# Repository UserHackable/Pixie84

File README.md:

## Pixie84 

### Board dimensions

* (160000, 80000) original units
* (1.6000, 0.8000) inches
* (40.6400, 20.3200) mm

| Front | Back |
| --- | --- |
|  |  |

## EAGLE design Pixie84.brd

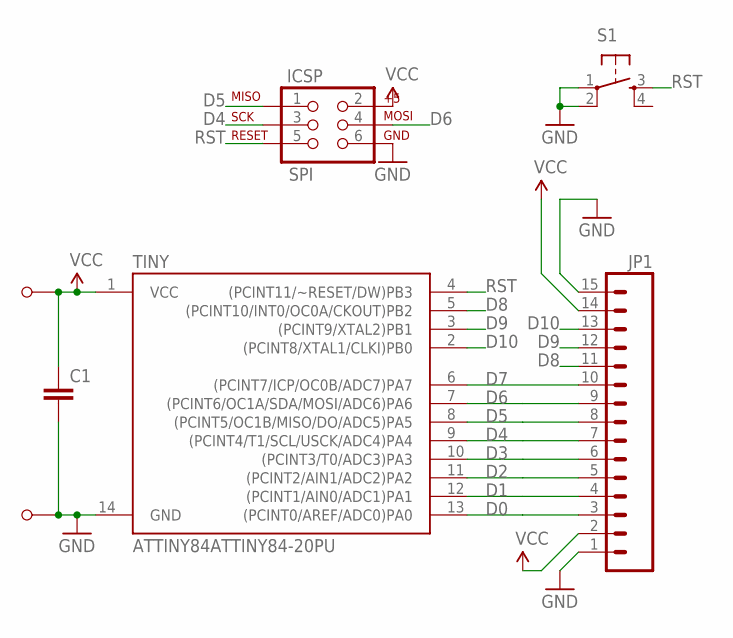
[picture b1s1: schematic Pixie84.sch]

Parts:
C1: CAPPTH; CAP-PTH-SMALL
ICSP: SPI; 2X3-NS
JP1: M15; 1X15
S1: TAC_SWITCHPTH; TACTILE-PTH
TINY: ATTINY84ATTINY84-20PU; DIL14
U$1, U$2: M1; M1_NO_STRAIN

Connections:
D0: JP1.3, TINY.13 ((PCINT0/AREF/ADC0)PA0)
D1: JP1.4, TINY.12 ((PCINT1/AIN0/ADC1)PA1)
D2: JP1.5, TINY.11 ((PCINT2/AIN1/ADC2)PA2)
D3: JP1.6, TINY.10 ((PCINT3/T0/ADC3)PA3)
D4: ICSP.3 (SCK), JP1.7, TINY.9 ((PCINT4/T1/SCL/USCK/ADC4)PA4)
D5: ICSP.1 (MISO), JP1.8, TINY.8 ((PCINT5/OC1B/MISO/DO/ADC5)PA5)
D6: ICSP.4 (MOSI), JP1.9, TINY.7 ((PCINT6/OC1A/SDA/MOSI/ADC6)PA6)
D7: JP1.10, TINY.6 ((PCINT7/ICP/OC0B/ADC7)PA7)
D8: JP1.11, TINY.5 ((PCINT10/INT0/OC0A/CKOUT)PB2)
D9: JP1.12, TINY.3 ((PCINT9/XTAL2)PB1)
D10: JP1.13, TINY.2 ((PCINT8/XTAL1/CLKI)PB0)
GND: C1.2, ICSP.6 (GND), JP1.1, JP1.15, S1.1, S1.2, TINY.14 (GND), U$2.P$1
RST: ICSP.5 (RST), S1.3, TINY.4 ((PCINT11/~RESET/DW)PB3)
VCC: C1.1, ICSP.2 (V+), JP1.2, JP1.14, TINY.1 (VCC), U$1.P$1

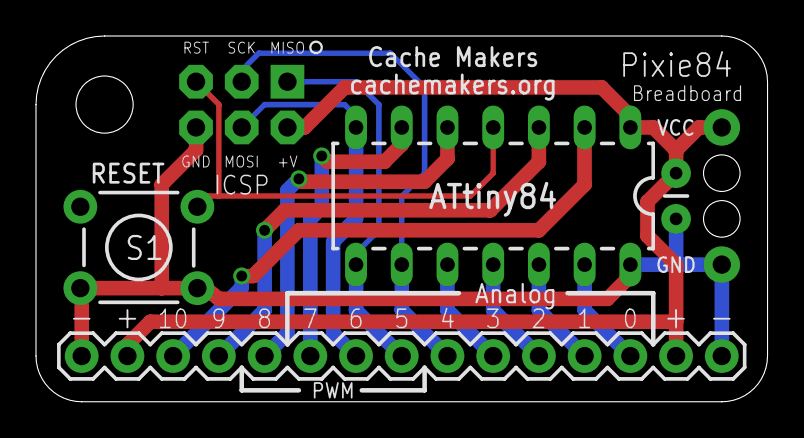
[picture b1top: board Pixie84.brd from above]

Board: 2 copper layers, 40.6 x 20.3 mm, 7 parts (0 on the bottom side), 14 nets.

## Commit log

2016-04-06 updating makefile
2016-04-06 cleaning out gerbers
2016-04-06 updating
2016-04-07 from Makefile

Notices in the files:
parts and their libraries:
SparkFun-DigitalIC: Licensing: Creative Commons ShareAlike 4.0 International - https://creativecommons.org/licenses/by-sa/4.0
